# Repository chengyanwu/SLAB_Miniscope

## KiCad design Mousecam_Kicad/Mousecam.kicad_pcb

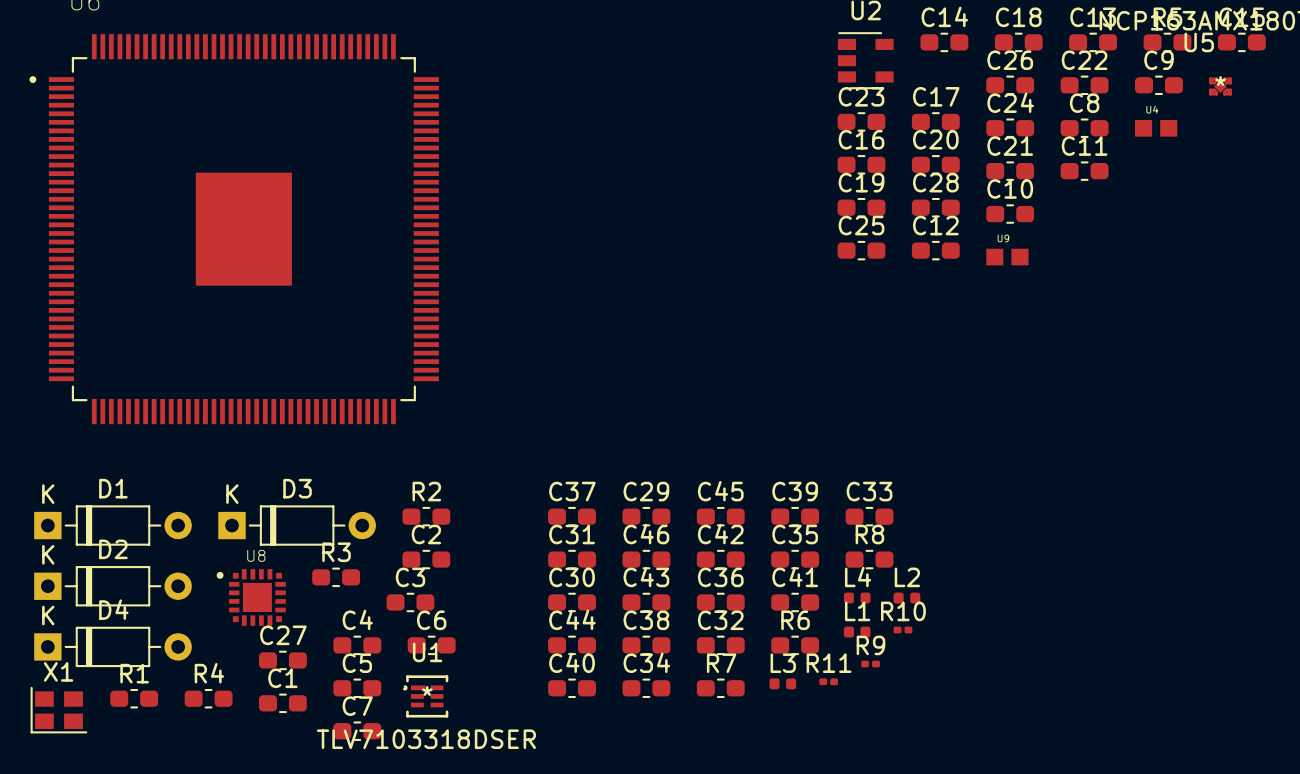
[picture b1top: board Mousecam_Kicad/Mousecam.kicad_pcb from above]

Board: 2 copper layers, 73 parts (0 on the bottom side), 23 nets, no tracks yet.

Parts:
C1, C2, C3, C26, C28, C31, C33: 1uF; C_0603_1608Metric_Pad1.05x0.95mm_HandSolder
C4, C5, C6, C7: 10pF; C_0603_1608Metric_Pad1.05x0.95mm_HandSolder
C8, C9, C10, C11, C12, C13, C14, C15, C16, C17, C18, C19, C20, C21, C24, C27, C29, C37, C38, C39, C40, C41: 0.1uF; C_0603_1608Metric_Pad1.05x0.95mm_HandSolder
C22, C23, C30, C32, C36: 10uF; C_0603_1608Metric_Pad1.05x0.95mm_HandSolder
C25, C34, C35: 4.7uF; C_0603_1608Metric_Pad1.05x0.95mm_HandSolder
C42, C43, C44, C45, C46: 0.01uF; C_0603_1608Metric_Pad1.05x0.95mm_HandSolder
D1, D2, D3, D4: 1N4148; D_DO-35_SOD27_P7.62mm_Horizontal
L1: 100uH; L_0402_1005Metric
L2: 4.7uH; L_0402_1005Metric
L3, L4: 1kohm; L_0402_1005Metric
R1, R4: 10k; R_0603_1608Metric_Pad1.05x0.95mm_HandSolder
R2: DNL; R_0603_1608Metric_Pad1.05x0.95mm_HandSolder
R3: 1k; R_0603_1608Metric_Pad1.05x0.95mm_HandSolder
R5: 47.7 kOhm; R_0603_1608Metric_Pad1.05x0.95mm_HandSolder
R6, R7: 1K; R_0603_1608Metric_Pad1.05x0.95mm_HandSolder
R8: 49.9; R_0603_1608Metric_Pad1.05x0.95mm_HandSolder
R9, R11: 10K; R_0201_0603Metric
R10: 100K; R_0201_0603Metric
U1: TLV7103318DSER
U2: LM321; SOT-23-5
U4, U9: BLM18AG601SN1D
U5: NCP163AMX180TBG
U6: 10M50SCE144C8G; QFP50P2200X2200X165_145N
U8: Si5350c; QFN50P300X300X60-21N
X1: SG-210STF; Oscillator_SMD_SeikoEpson_SG210-4Pin_2.5x2.0mm

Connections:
+1V8: C2.1, C9.1, C12.1, C15.1, C18.1, C23.1, C34.2, C37.1, C40.1, C41.1, C42.1, C45.1, C46.1, L3.2, L4.2, R9.1, R11.1, U1.5, U2.1
+3V3: C3.1, C8.1, C10.1, C13.1, C17.1, C20.1, C21.1, C27.1, D1.1, D2.1, D3.1, D4.1, R1.1, R2.2, R4.1, U1.6, U6.9, U6.24, U6.31, U6.45, U6.54, U6.67, U6.78, U6.94, U6.103, U6.113, U6.122, U6.139, U8.10, U8.11, U8.14, U8.18, U8.20, X1.4
+5V: C1.1, C14.1, C26.1, C30.1, C32.1, L2.2, R7.1, U1.1, U1.2, U1.3, U2.5, U5.3, U5.4
/CLK_PLL: U8.6, X1.3
/FPGA/TCK: C7.1, D4.2, R3.1, U6.17
/FPGA/TDI: C4.1, D1.2, R1.2, U6.18
/FPGA/TDO: C5.1, D2.2, U6.19
/FPGA/TMS: C6.1, D3.2, R4.2, U6.16
/FPGA/VCC_ONE: U6.1, U6.36, U6.37, U6.47, U6.72, U6.73, U6.108, U6.109, U6.114, U6.144
/Python480/VDD_PIX: C11.1, C16.1, C19.1, C22.1, U9.1
/Python480/VDD_PIX_3V3: C28.1, U5.1, U9.2
/Python480/VREF_BOTPLATE: C24.1, C25.1, U4.1
/Serializer/DOUT_P: C29.1, L1.1, R6.2
/Serializer/MODE: R9.2, R10.1
/Serializer/PDB: C33.1, R11.2
/Serializer/VDDCML: C36.1, C39.1, C44.1, L4.1
/Serializer/VDDPLL: C35.2, C38.1, C43.1, L3.1
GND: C1.2, C2.2, C3.2, C4.2, C5.2, C6.2, C7.2, C8.2, C9.2, C10.2, C11.2, C12.2, C13.2, C14.2, C15.2, C16.2, C17.2, C18.2, C19.2, C20.2, C21.2, C22.2, C23.2, C24.2, C25.2, C27.2, C28.2, C30.2, C32.2, C33.2, C34.1, C35.1, C36.2, C37.2, C38.2, C39.2, C40.2, C41.2, C42.2, C43.2, C44.2, C45.2, C46.2, R3.2, R5.2, R8.1, R10.2, U1.4, U2.2, U6.3, U6.4, U6.48, U6.56, U6.59, U6.68, U6.79, U6.95, U6.104, U6.112, U6.115, U6.121, U6.137, U6.142, U8.3, U8.4, U8.5, U8.7, U8.21, X1.2
unnamed: C26.2, U5.2, U5.5
unnamed: C31.1, R8.2
unnamed: L1.2, L2.1, R6.1, R7.2
unnamed: R2.1, X1.1
unnamed: U2.3, U2.4, U4.2

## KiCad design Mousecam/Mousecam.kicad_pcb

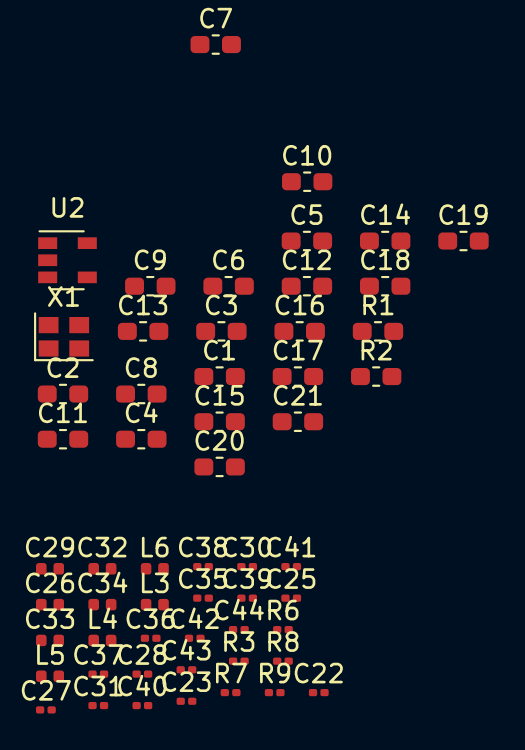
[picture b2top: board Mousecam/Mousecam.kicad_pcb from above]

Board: 2 copper layers, 56 parts (0 on the bottom side), 16 nets, no tracks yet.

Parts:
C1, C2, C3, C4, C5, C6, C7, C8, C9, C10, C11, C12, C13, C14, C15, C16, C17, C18, C19, C20, C21: GRM033R61A104ME15D; C_0603_1608Metric_Pad1.05x0.95mm_HandSolder
C22, C27, C35, C36, C37, C38, C39: 0.1uF; C_0201_0603Metric
C23: 0.047uF; C_0201_0603Metric
C25, C28, C30, C31: 1uF; C_0201_0603Metric
C26, C29, C34: 10uF; C_0402_1005Metric
C32, C33: 4.7uF; C_0402_1005Metric
C40, C41, C42, C43, C44: 0.01uF; C_0201_0603Metric
L3: 100uH; L_0402_1005Metric
L4: 4.7uH; L_0402_1005Metric
L5, L6: 1kohm; L_0402_1005Metric
R1: ERJ-1GEF1022C; R_0603_1608Metric_Pad1.05x0.95mm_HandSolder
R2: DNL; R_0603_1608Metric_Pad1.05x0.95mm_HandSolder
R3: 50; R_0201_0603Metric
R6: 49.9; R_0201_0603Metric
R7, R9: 10K; R_0201_0603Metric
R8: 100K; R_0201_0603Metric
U2: LM321; SOT-23-5
X1: SG-210STF; Oscillator_SMD_SeikoEpson_SG210-4Pin_2.5x2.0mm

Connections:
+1V8: C2.1, C6.1, C10.1, C13.1, C16.1, C25.1, C32.2, C35.2, C38.2, C39.2, C40.2, C43.2, C44.2, L5.2, L6.2, R7.1, R9.1, U2.1
+3V3: C1.1, C3.1, C4.1, C8.1, C11.1, C14.1, C21.2, C30.1, R2.2, X1.4
+5V: C7.1, C19.2, C26.2, C29.1, L4.2, U2.5
/Python480/VDD_PIX: C5.1, C9.1, C12.1, C15.1
/Python480/VREF_BOTPLATE: C17.1, C18.1
/Serializer/DOUT_P: C22.1, C27.1, L3.1
/Serializer/MODE: R7.2, R8.1
/Serializer/PDB: C31.1, R9.2
/Serializer/VDDCML: C34.2, C37.2, C42.2, L6.1
/Serializer/VDDPLL: C33.2, C36.2, C41.2, L5.1
GND: C1.2, C2.2, C3.2, C4.2, C5.2, C6.2, C7.2, C8.2, C9.2, C10.2, C11.2, C12.2, C13.2, C14.2, C15.2, C16.2, C17.2, C18.2, C19.1, C20.2, C21.1, C25.2, C26.1, C29.2, C30.2, C31.2, C32.1, C33.1, C34.1, C35.1, C36.1, C37.1, C38.1, C39.1, C40.1, C41.1, C42.1, C43.1, C44.1, R1.2, R3.2, R6.2, R8.2, U2.2, X1.2
unnamed: C23.2, R3.1
unnamed: C28.1, R6.1
unnamed: U2.3, U2.4
unnamed: L3.2, L4.1
unnamed: R2.1, X1.1

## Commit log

2021-01-05 commit message
2021-03-25 sync
2021-04-20 cleared up folders
2021-04-29 IW, add UART with OV7725 verilog code
2021-04-29 updated relative path for libs
2021-05-03 add HDMI demo
2021-05-07 IW, add hdmi
2021-05-15 IW, syn

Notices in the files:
parts and their libraries:
Copyright 2016 Accelerated Designs. All rights reserved.
